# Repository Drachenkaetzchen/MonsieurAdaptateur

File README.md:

MonsieurAdaptateur is an adapter which lets you adapt between different commonly used plugs (4mm, 2mm, BNC, standard male and female pin headers, faston 6.3mm and 4.75mm, DC 2.1mm jack, scope probe).

Please see the [product page](http://felitek.de/monsieur-adaptateur/) for further details.

Schematic and board layout were done using Eagle 6.5.

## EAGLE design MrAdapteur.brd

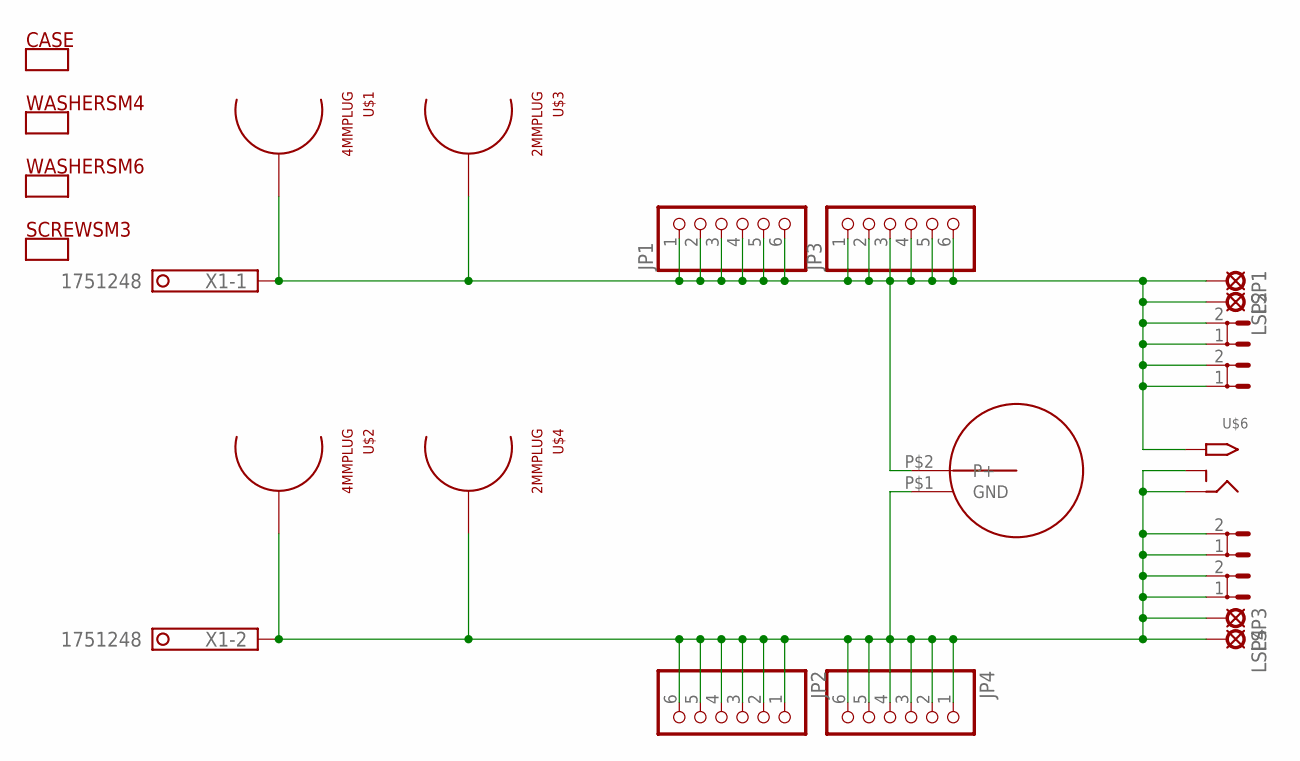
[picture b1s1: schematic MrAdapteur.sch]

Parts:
JP1, JP2, JP3, JP4: PINHD-1X6; 1X06
LSP1, LSP2, LSP3, LSP4: LSP11
U$1, U$2: 4MMPLUG
U$3, U$4: 2MMPLUG
U$5: BNC
U$6: 2.1MMJACKTHM; PJ-102A
X1: 1751248
X3, X4, X5, X6: ST4,8

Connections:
unnamed: JP1.1, JP1.2, JP1.3, JP1.4, JP1.5, JP1.6, JP3.1, JP3.2, JP3.3, JP3.4, JP3.5, JP3.6, LSP1.MP, LSP2.MP, U$1.P$1, U$3.P$1, U$5.P$2 (P+), U$6.TIP, X1.1, X3.1, X3.2, X5.1, X5.2
unnamed: JP2.1, JP2.2, JP2.3, JP2.4, JP2.5, JP2.6, JP4.1, JP4.2, JP4.3, JP4.4, JP4.5, JP4.6, LSP3.MP, LSP4.MP, U$2.P$1, U$4.P$1, U$5.P$1 (GND), U$6.RING, U$6.RING_SW, X1.2, X4.1, X4.2, X6.1, X6.2

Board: 2 copper layers, 20 parts (0 on the bottom side), 2 nets, no tracks yet.

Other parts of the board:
U$7: OSHW-LOGO-L

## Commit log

2014-02-08 Cleaned up silkscreen
2014-02-08 Added standard DC jack, 4.75mm flat connector and wire loop for attaching alligator clips or scope probes
2014-02-08 Fixed silkscreen for pcb screw terminal
2014-02-08 Replaced DC connector with the adafruit one for bigger holes
2014-02-08 Added larger pads for the BNC connector
2014-02-08 Several minor fixes (sorry, can't remember them) ;)
2014-02-09 Replaced via with proper solder point
2014-02-09 Added notice to the product page and documentation
2014-02-10 Updated silkscreen to reflect correct name
2014-02-10 Fixed name in the readme as well
2014-02-15 Fixed hole size for wire clips, added stop mask for the UL/Manufacturing marks
2014-02-23 Added license and information in which format the schematic and board are in, removed placeholder for manufacturing marks

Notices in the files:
parts and their libraries:
SparkFun: Licensing: CC v3.0 Share-Alike You are welcome to use this library for commercial purposes.
